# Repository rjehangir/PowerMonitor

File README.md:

PowerMonitor
============

Arduino-based power monitoring board with 4 channels for the SolarSurfer.

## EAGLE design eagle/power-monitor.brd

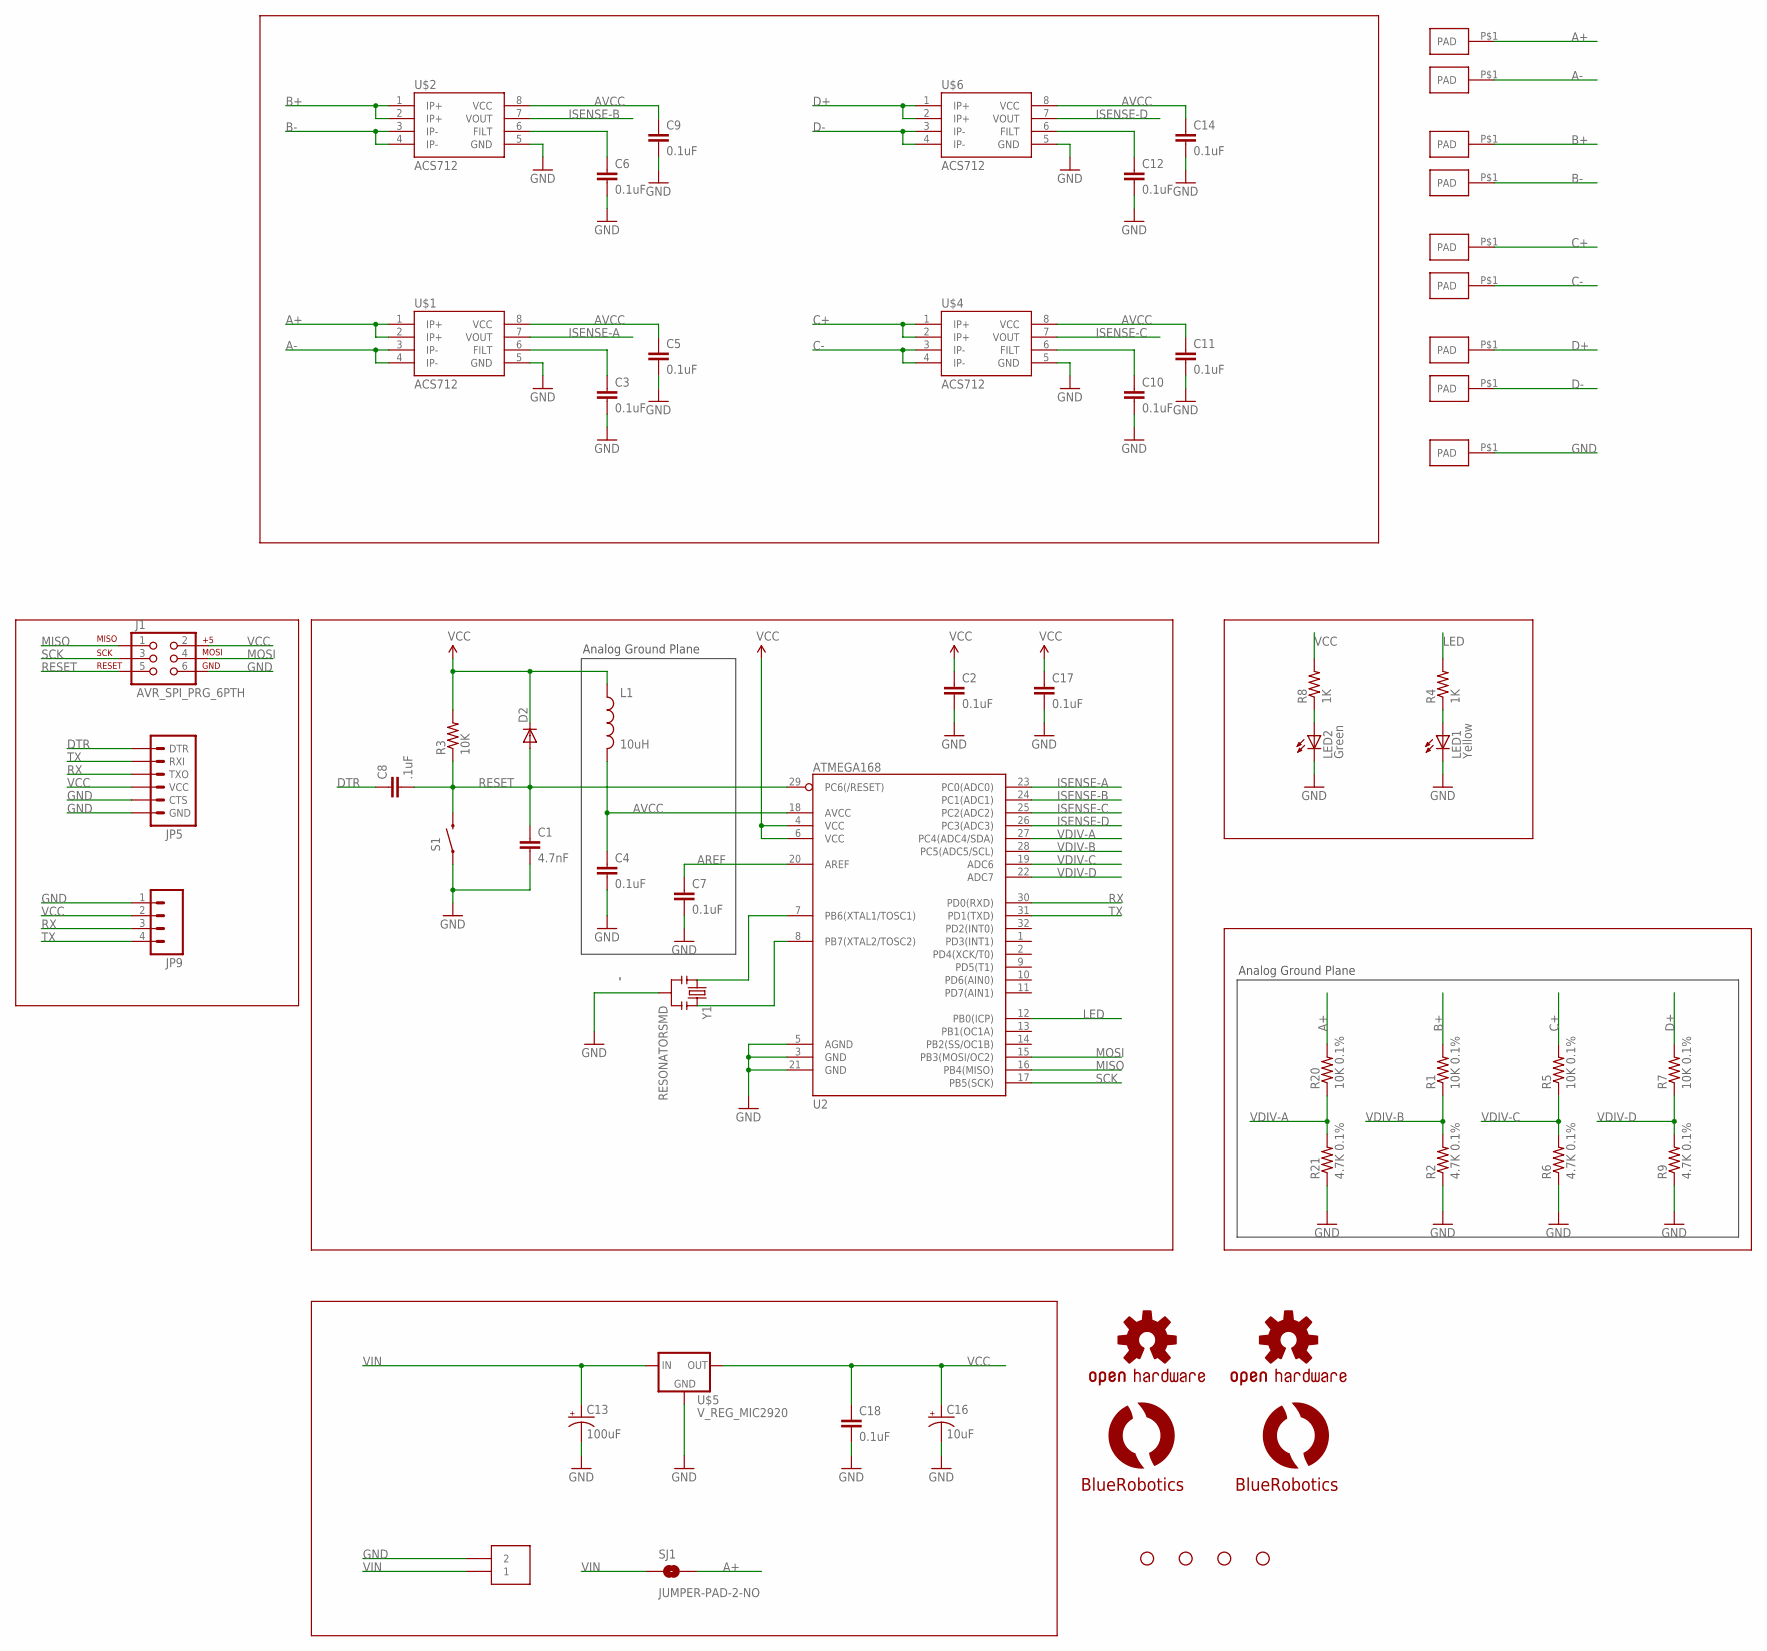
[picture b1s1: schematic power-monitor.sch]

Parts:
C1: 4.7nF; 0603-CAP
C2, C3, C4, C5, C6, C7, C9, C10, C11, C12, C14, C17, C18: 0.1uF; 0603-CAP
C8: .1uF; 0603-CAP
C13: 100uF; CPOL-RADIAL-100UF-25V
C16: 10uF; EIA3216
D2: DIODESOD; SOD-323
J1: AVR_SPI_PRG_6PTH; 2X3
JP5: ARDUINO_SERIAL_PROGRAMPTH; 1X06
JP9: M04PTH; 1X04
L1: 10uH; 0603
LED1: Yellow; LED-0603
LED2: Green; LED-0603
LOGO1: OSHW-LOGOS; OSHW-LOGO-S
LOGO2: OSHW-LOGOM; OSHW-LOGO-M
R1, R5, R7, R20: 10K 0.1%; 0603-RES
R2, R6, R9, R21: 4.7K 0.1%; 0603-RES
R3: 10K; 0603-RES
R4, R8: 1K; 0603-RES
S1: reset; TACTILE_SWITCH_SMD
SJ1: JUMPER-PAD-2-NO; PAD-JUMPER-2-NO_NO_SILK
STANDOFF1, STANDOFF2, STANDOFF3, STANDOFF4: STAND-OFF
U2: ATMEGA168; TQFP32-08
U$1, U$2, U$4, U$6: ACS712; SO08
U$3: TERMINAL-25MM-WEID; LSF-SMT-5MM-2
U$5: V_REG_MIC2920; SOT223
U$7, U$8, U$9, U$10, U$11, U$13, U$14, U$15, U$16: PADLARGE-ONE-SIDE; PAD-0.2X0.3-ONE-SIDE
U$17: LOGOBR-LOGO-M; BR-LOGO-MEDIUM
U$18: LOGOBR-LOGO-S; BR-LOGO-SMALL
Y1: RESONATORSMD; RESONATOR-SMD

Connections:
A+: R20.2, SJ1.2, U$1.1 (IP+), U$1.2 (IP+), U$13.P$1
A-: U$1.3 (IP-), U$1.4 (IP-), U$14.P$1
AREF: C7.1, U2.20 (AREF)
AVCC: C4.1, C5.1, C9.1, C11.1, C14.1, L1.2, U2.18 (AVCC), U$1.8 (VCC), U$2.8 (VCC), U$4.8 (VCC), U$6.8 (VCC)
B+: R1.2, U$2.1 (IP+), U$2.2 (IP+), U$15.P$1
B-: U$2.3 (IP-), U$2.4 (IP-), U$16.P$1
C+: R5.2, U$4.1 (IP+), U$4.2 (IP+), U$7.P$1
C-: U$4.3 (IP-), U$4.4 (IP-), U$8.P$1
D+: R7.2, U$6.1 (IP+), U$6.2 (IP+), U$9.P$1
D-: U$6.3 (IP-), U$6.4 (IP-), U$10.P$1
DTR: C8.1, JP5.1 (DTR)
GND: C1.2, C2.2, C3.2, C4.2, C5.2, C6.2, C7.2, C9.2, C10.2, C11.2, C12.2, C13.2 (-), C14.2, C16.C (-), C17.2, C18.2, J1.6, JP5.5 (CTS), JP5.6 (GND), JP9.1, LED1.C, LED2.C, R2.1, R6.1, R9.1, R21.1, S1.1, U2.3 (GND), U2.5 (AGND), U2.21 (GND), U$1.5 (GND), U$2.5 (GND), U$3.2, U$3.4 (2), U$4.5 (GND), U$5.2 (GND), U$6.5 (GND), U$11.P$1, Y1.2
ISENSE-A: U2.23 (PC0(ADC0)), U$1.7 (VOUT)
ISENSE-B: U2.24 (PC1(ADC1)), U$2.7 (VOUT)
ISENSE-C: U2.25 (PC2(ADC2)), U$4.7 (VOUT)
ISENSE-D: U2.26 (PC3(ADC3)), U$6.7 (VOUT)
LED: R4.2, U2.12 (PB0(ICP))
MISO: J1.1, U2.16 (PB4(MISO))
MOSI: J1.4, U2.15 (PB3(MOSI/OC2))
unnamed: C6.1, U$2.6 (FILT)
unnamed: C3.1, U$1.6 (FILT)
unnamed: LED1.A, R4.1
unnamed: C10.1, U$4.6 (FILT)
unnamed: C12.1, U$6.6 (FILT)
unnamed: U2.7 (PB6(XTAL1/TOSC1)), Y1.1
unnamed: U2.8 (PB7(XTAL2/TOSC2)), Y1.3
unnamed: LED2.A, R8.1
RESET: C1.1, C8.2, D2.2 (A), J1.5, R3.1, S1.3 (2), U2.29 (PC6(/RESET))
RX: JP5.3 (TXO), JP9.3, U2.30 (PD0(RXD))
SCK: J1.3, U2.17 (PB5(SCK))
TX: JP5.2 (RXI), JP9.4, U2.31 (PD1(TXD))
VCC: C2.1, C16.A (+), C17.1, C18.1, D2.1 (C), J1.2, JP5.4 (VCC), JP9.2, L1.1, R3.2, R8.2, U2.4 (VCC), U2.6 (VCC), U$5.3 (OUT)
VDIV-A: R20.1, R21.2, U2.27 (PC4(ADC4/SDA))
VDIV-B: R1.1, R2.2, U2.28 (PC5(ADC5/SCL))
VDIV-C: R5.1, R6.2, U2.19 (ADC6)
VDIV-D: R7.1, R9.2, U2.22 (ADC7)
VIN: C13.1 (+), SJ1.1, U$3.1, U$3.3 (1), U$5.1 (IN)

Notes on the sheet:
Analog Ground Plane

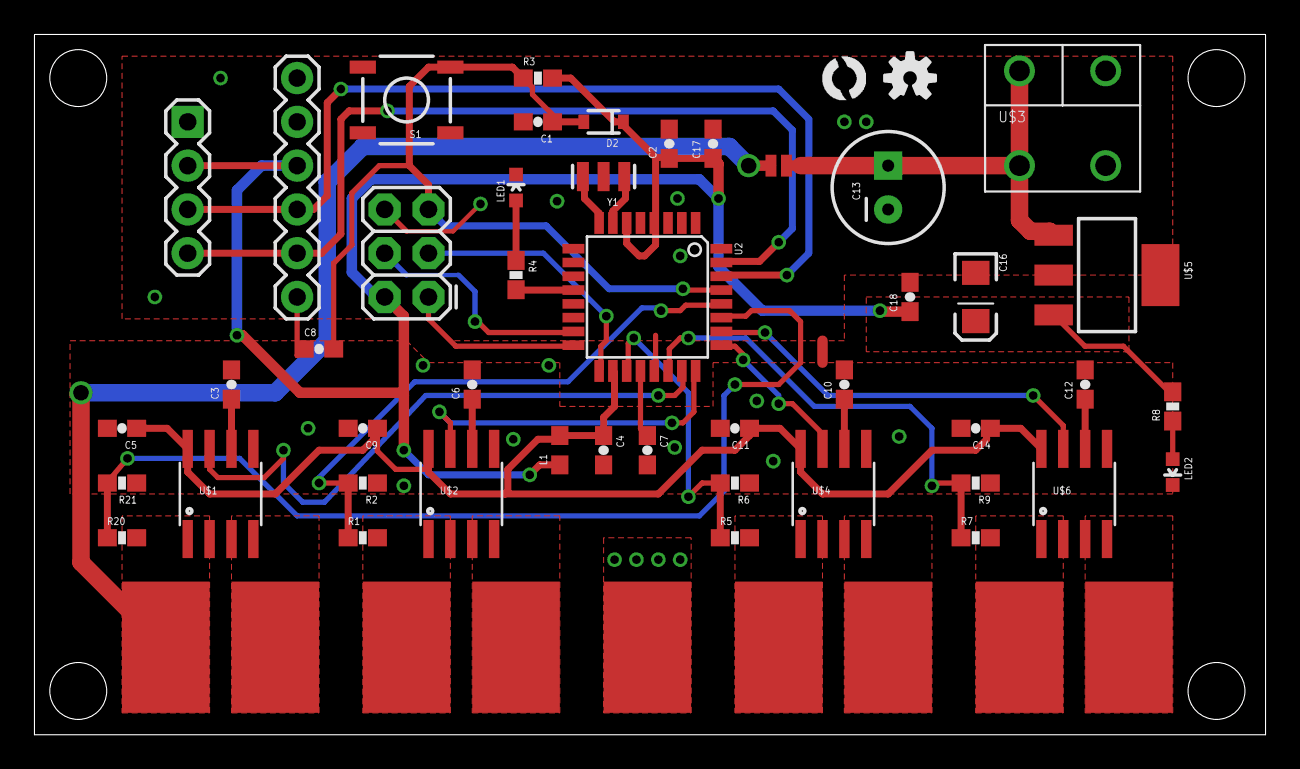
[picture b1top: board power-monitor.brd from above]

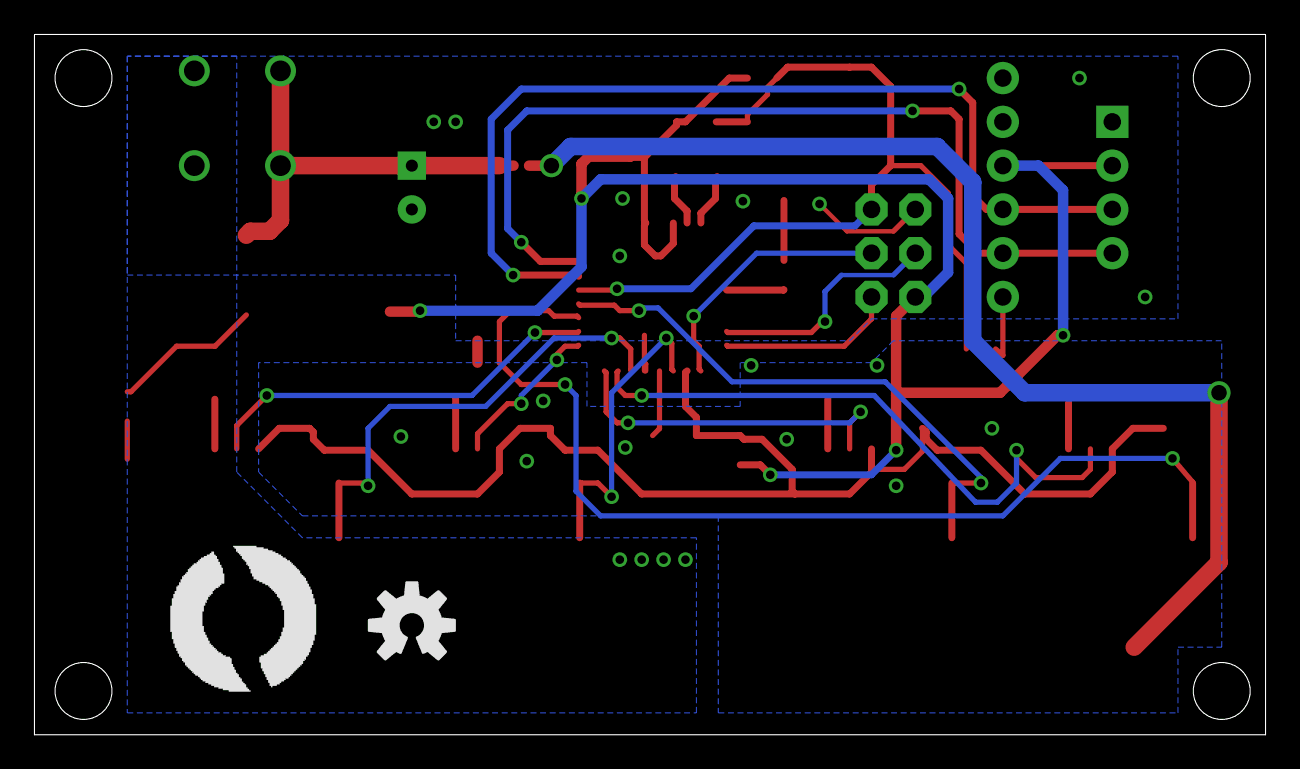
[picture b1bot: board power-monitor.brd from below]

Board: 2 copper layers, 71.4 x 40.6 mm, 62 parts (2 on the bottom side), 37 nets.

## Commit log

2014-07-19 Added initial files.
2014-07-24 Tested the power monitor code successfully.
2014-09-27 Added Eagle files for the PowerMonitor board.

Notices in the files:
parts and their libraries:
SparkFun-AnalogIC: Licensing:Creative Commons ShareAlike 4.0 International - https://creativecommons.org/licenses/by-sa/4.0
